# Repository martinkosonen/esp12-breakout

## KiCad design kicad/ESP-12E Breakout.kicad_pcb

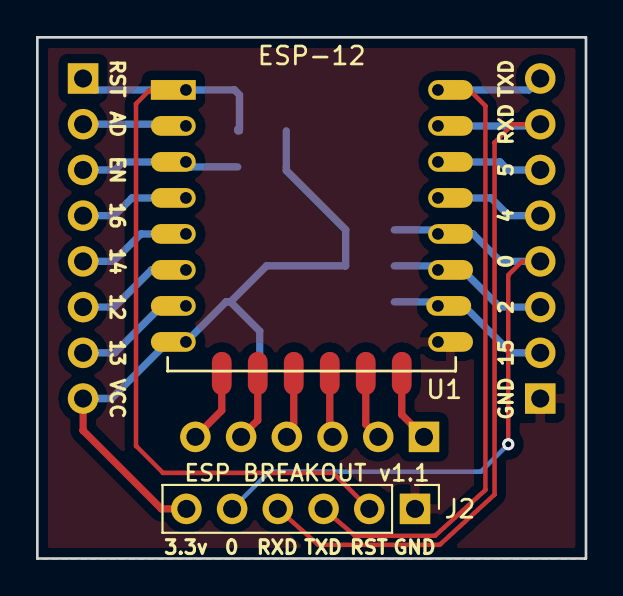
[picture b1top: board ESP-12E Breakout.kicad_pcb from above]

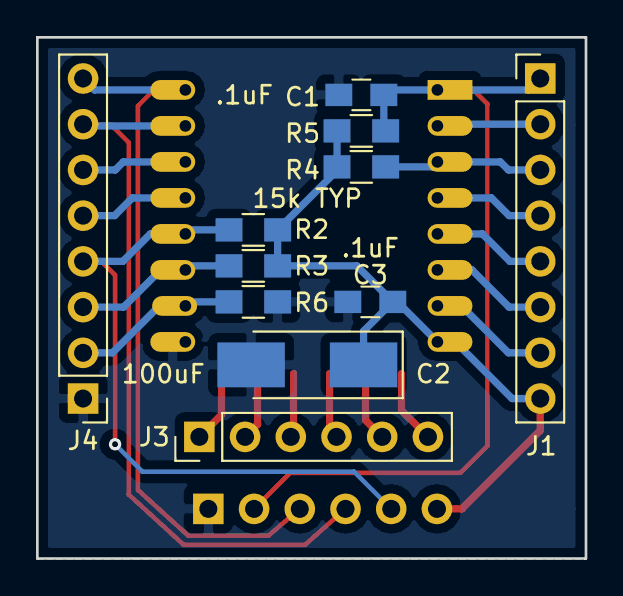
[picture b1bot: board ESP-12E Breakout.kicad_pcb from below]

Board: 2 copper layers, 30.5 x 29.0 mm, 13 parts (11 on the bottom side), 22 nets.

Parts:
C1, C3: .1uF; C_0805_HandSoldering
C2: 100uF; CP_Tantalum_Case-C_EIA-6032-28_Hand
J1: P1-8; Pin_Header_Straight_1x08_Pitch2.54mm
J2: CONN_01X06; Socket_Strip_Straight_1x06_Pitch2.54mm
J3: P17-22; Pin_Header_Straight_1x06_Pitch2.54mm
J4: P8-16; Pin_Header_Straight_1x08_Pitch2.54mm
R2: 15k TYP; R_0805_HandSoldering
R3, R4, R5, R6: 15k; R_0805_HandSoldering
U1: ESP-12; ESP-12E

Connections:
+3V3: C2.1, C3.1, J1.8, J2.6, R2.2, R3.2, R4.2, R5.2, U1.8
ADC: J1.2, U1.2
CS0: J3.6, U1.17
EN: J1.3, R4.1, U1.3
GND: C1.2, C2.2, C3.2, J2.1, J4.1, R6.2, U1.9
GPIO0: J2.5, J4.4, R2.1, U1.12
GPIO2: J4.3, R3.1, U1.11
GPIO4: J4.5, U1.13
GPIO5: J4.6, U1.14
GPIO9: J3.4, U1.19
GPIO10: J3.3, U1.20
GPIO12: J1.6, U1.6
GPIO13: J1.7, U1.7
GPIO14: J1.5, U1.5
GPIO15: J4.2, R6.1, U1.10
GPIO16: J1.4, U1.4
MISO: J3.5, U1.18
MOSI: J3.2, U1.21
RXD: J2.4, J4.7, U1.15
SCLK: J3.1, U1.22
TXD: J2.3, J4.8, U1.16
nRST: C1.1, J1.1, J2.2, R5.1, U1.1

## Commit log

2018-08-20 Create LICENSE
2018-08-20 Rename ESP-12E Breakout.kicad_pcb to kicad/ESP-12E Breakout.kicad_pcb
2018-08-20 Rename ESP-12E Breakout.net to kicad/ESP-12E Breakout.net
2018-08-20 Rename ESP-12E Breakout.pro to kicad/ESP-12E Breakout.pro
2018-08-20 Rename ESP-12E Breakout.sch to kicad/ESP-12E Breakout.sch
